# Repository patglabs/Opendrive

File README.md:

# Opendrive
This is currently the first prototype for a open source Field-Oriented Control Electronic Speed Controller.

I am currently designing it to be able to drive 300w motors at 12v (or 3s).

This doesnt mean these are limitation. With good cooling they should be able to handle quite a bit more.

It's designed to be used on a robotic arm I'm working on.

For Groundplane:
the template gives a 404

UPDATE:
yeah its gonna be too expensive nvm

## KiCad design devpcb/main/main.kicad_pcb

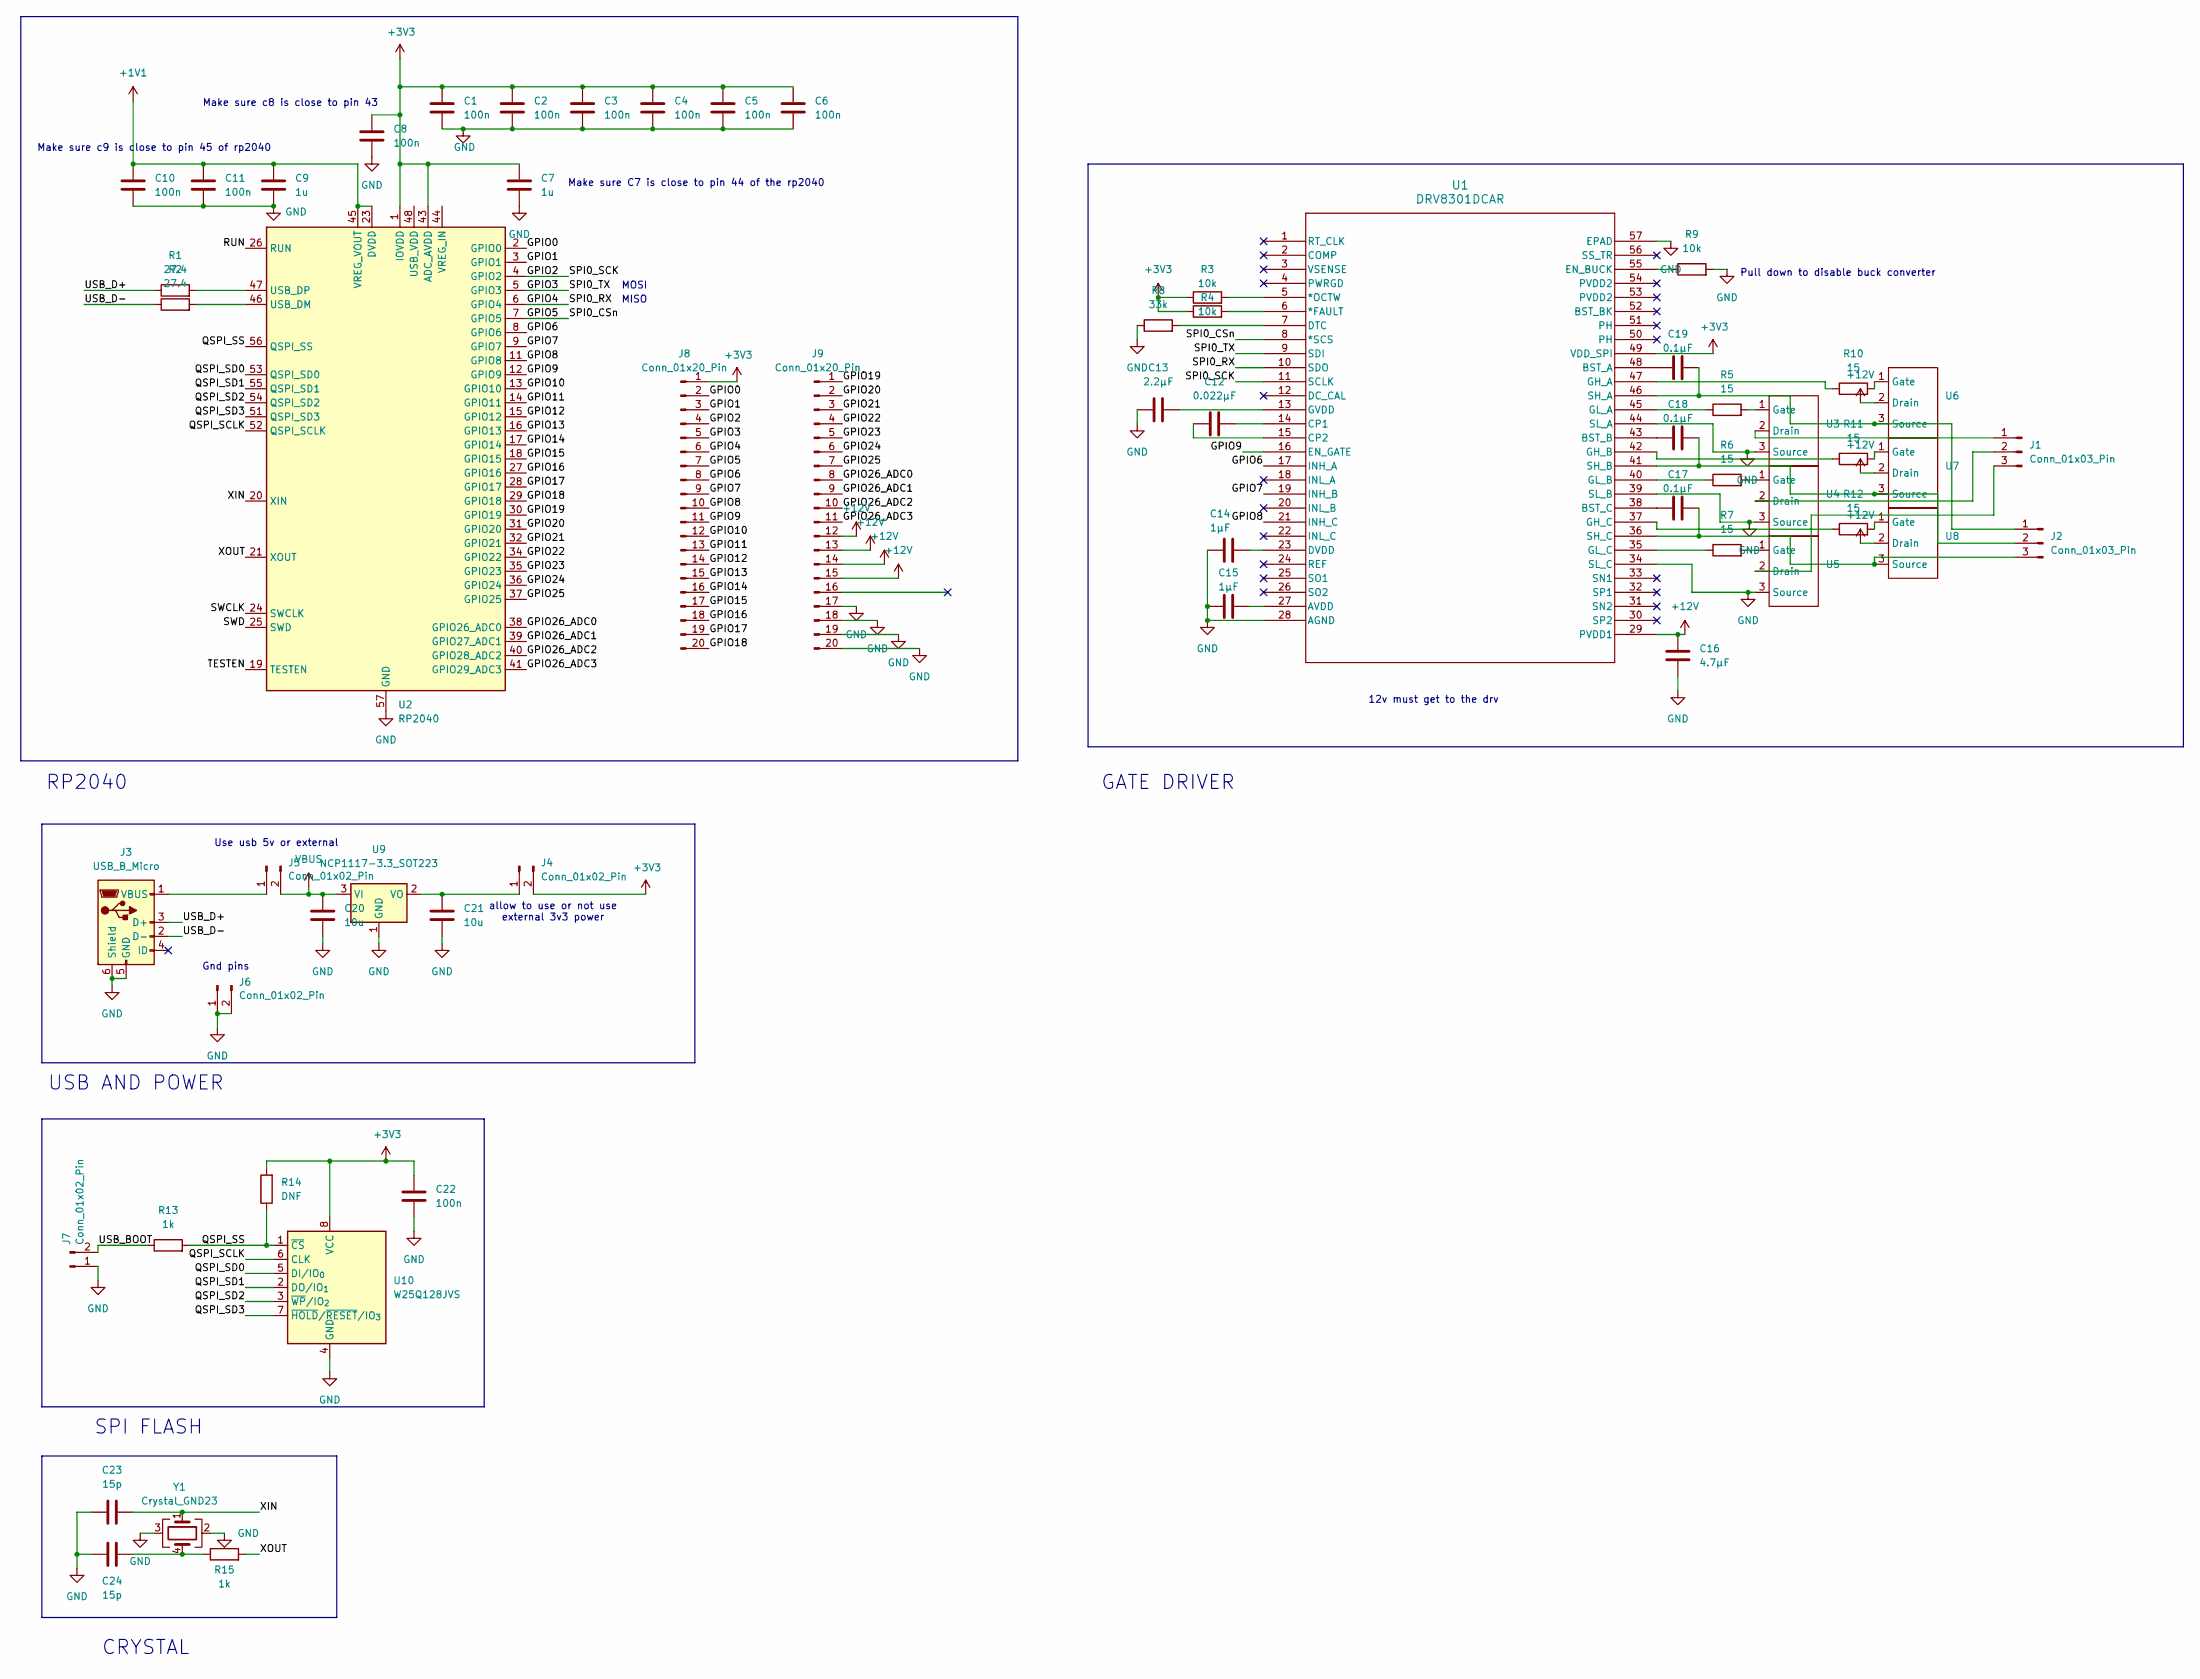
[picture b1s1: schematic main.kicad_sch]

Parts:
C1, C2, C3, C4, C5, C6, C8, C10, C11, C22: 100n; C_0402_1005Metric
C7, C9: 1u; C_0603_1608Metric
C12: 0.022µF; C_0402_1005Metric_Pad0.74x0.62mm_HandSolder
C13: 2.2µF; C_0805_2012Metric
C14, C15: 1µF; C_0603_1608Metric
C16: 4.7µF; C_0805_2012Metric
C17, C18, C19: 0.1µF; C_0603_1608Metric
C20, C21: 10u; C_0805_2012Metric
C23, C24: 15p; C_0402_1005Metric
J1, J2: Conn_01x03_Pin; PinHeader_1x03_P2.54mm_Vertical
J3: USB_B_Micro; USB_Micro-AB_Molex_47590-0001
J4, J5, J6, J7: Conn_01x02_Pin; PinHeader_1x02_P2.54mm_Vertical
J8, J9: Conn_01x20_Pin; PinHeader_1x20_P2.54mm_Vertical
R1, R2: 27.4; R_0402_1005Metric
R3, R4, R9: 10k; R_0402_1005Metric
R5, R6, R7, R10, R11, R12: 15; R_0402_1005Metric
R8: 33k; R_0402_1005Metric
R13, R15: 1k; R_0402_1005Metric
R14: DNF; R_0402_1005Metric
U1: DRV8301DCAR; DCA56_6P35X3P61
U2: RP2040; QFN-56-1EP_7x7mm_P0.4mm_EP3.2x3.2mm
U3, U4, U5, U6, U7, U8: TO-220-3_Vertical
U9: NCP1117-3.3_SOT223; SOT-223-3_TabPin2
U10: W25Q128JVS; SOIC-8_5.3x5.3mm_P1.27mm
Y1: Crystal_GND23; Crystal_SMD_3225-4Pin_3.2x2.5mm

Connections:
+1V1: C9.1, C10.1, C11.1, U2.23 (DVDD), U2.45 (VREG_VOUT), U2.50 (DVDD)
+3V3: C1.1, C2.1, C3.1, C4.1, C5.1, C6.1, C7.1, C8.1, C22.1, J4.2, J8.1, R3.1, R4.1, R14.2, U1.49 (VDD_SPI), U2.1 (IOVDD), U2.10 (IOVDD), U2.22 (IOVDD), U2.33 (IOVDD), U2.42 (IOVDD), U2.43 (ADC_AVDD), U2.49 (IOVDD), U10.8 (VCC)
+12V: C16.1, J9.12, J9.13, J9.14, J9.15, U1.29 (PVDD1), U6.2 (Drain), U7.2 (Drain), U8.2 (Drain)
/GPIO0: J8.2, U2.2 (GPIO0)
/GPIO1: J8.3, U2.3 (GPIO1)
/GPIO2: J8.4, U1.11 (SCLK), U2.4 (GPIO2)
/GPIO3: J8.5, U1.9 (SDI), U2.5 (GPIO3)
/GPIO4: J8.6, U1.10 (SDO), U2.6 (GPIO4)
/GPIO5: J8.7, U1.8 (*SCS), U2.7 (GPIO5)
/GPIO6: J8.8, U1.17 (INH_A), U2.8 (GPIO6)
/GPIO7: J8.9, U1.19 (INH_B), U2.9 (GPIO7)
/GPIO8: J8.10, U1.21 (INH_C), U2.11 (GPIO8)
/GPIO9: J8.11, U1.16 (EN_GATE), U2.12 (GPIO9)
/GPIO10: J8.12, U2.13 (GPIO10)
/GPIO11: J8.13, U2.14 (GPIO11)
/GPIO12: J8.14, U2.15 (GPIO12)
/GPIO13: J8.15, U2.16 (GPIO13)
/GPIO14: J8.16, U2.17 (GPIO14)
/GPIO15: J8.17, U2.18 (GPIO15)
/GPIO16: J8.18, U2.27 (GPIO16)
/GPIO17: J8.19, U2.28 (GPIO17)
/GPIO18: J8.20, U2.29 (GPIO18)
/GPIO19: J9.1, U2.30 (GPIO19)
/GPIO20: J9.2, U2.31 (GPIO20)
/GPIO21: J9.3, U2.32 (GPIO21)
/GPIO22: J9.4, U2.34 (GPIO22)
/GPIO23: J9.5, U2.35 (GPIO23)
/GPIO24: J9.6, U2.36 (GPIO24)
/GPIO25: J9.7, U2.37 (GPIO25)
/GPIO26_ADC0: J9.8, U2.38 (GPIO26_ADC0)
/GPIO26_ADC1: J9.9, U2.39 (GPIO27_ADC1)
/GPIO26_ADC2: J9.10, U2.40 (GPIO28_ADC2)
/GPIO26_ADC3: J9.11, U2.41 (GPIO29_ADC3)
/QSPI_SCLK: U2.52 (QSPI_SCLK), U10.6 (CLK)
/QSPI_SD0: U2.53 (QSPI_SD0), U10.5 (DI/IO_{0})
/QSPI_SD1: U2.55 (QSPI_SD1), U10.2 (DO/IO_{1})
/QSPI_SD2: U2.54 (QSPI_SD2), U10.3 (~WP/IO_{2})
/QSPI_SD3: U2.51 (QSPI_SD3), U10.7 (~HOLD/~RESET/IO_{3})
/QSPI_SS: R13.2, R14.1, U2.56 (QSPI_SS), U10.1 (~CS)
/RUN: U2.26 (RUN)
/SWCLK: U2.24 (SWCLK)
/SWD: U2.25 (SWD)
/TESTEN: U2.19 (TESTEN)
/USB_BOOT: J7.2, R13.1
/USB_D+: J3.3 (D+), R1.1
/USB_D-: J3.2 (D-), R2.1
/XIN: C23.2, U2.20 (XIN), Y1.1
/XOUT: R15.2, U2.21 (XOUT)
GND: C1.2, C2.2, C3.2, C4.2, C5.2, C6.2, C7.2, C8.2, C9.2, C10.2, C11.2, C13.1, C14.1, C15.1, C16.2, C20.2, C21.2, C22.2, C23.1, C24.1, J3.5 (GND), J3.6 (Shield), J6.1, J6.2, J7.1, J9.17, J9.18, J9.19, J9.20, R8.1, R9.2, U1.28 (AGND), U1.34 (SL_C), U1.39 (SL_B), U1.44 (SL_A), U1.57 (EPAD), U2.57 (GND), U3.3 (Source), U4.3 (Source), U5.3 (Source), U9.1 (GND), U10.4 (GND), Y1.2, Y1.3
unnamed: C24.2, R15.1, Y1.4
unnamed: J1.1, U3.2 (Drain)
unnamed: J1.2, U4.2 (Drain)
unnamed: J1.3, U5.2 (Drain)
unnamed: C19.2, J2.1, U1.46 (SH_A), U6.3 (Source)
unnamed: C18.2, J2.2, U1.41 (SH_B), U7.3 (Source)
unnamed: C17.2, J2.3, U1.36 (SH_C), U8.3 (Source)
unnamed: J3.1 (VBUS), J5.1
unnamed: C21.1, J4.1, U9.2 (VO)
unnamed: R4.2, U1.6 (*FAULT)
unnamed: R3.2, U1.5 (*OCTW)
unnamed: C15.2, U1.27 (AVDD)
unnamed: C19.1, U1.48 (BST_A)
unnamed: C18.1, U1.43 (BST_B)
unnamed: C17.1, U1.38 (BST_C)
unnamed: C12.2, U1.14 (CP1)
unnamed: C12.1, U1.15 (CP2)
unnamed: R8.2, U1.7 (DTC)
unnamed: C14.2, U1.23 (DVDD)
unnamed: R9.1, U1.55 (EN_BUCK)
unnamed: R10.1, U1.47 (GH_A)
unnamed: R11.1, U1.42 (GH_B)
unnamed: R12.1, U1.37 (GH_C)
unnamed: R5.1, U1.45 (GL_A)
unnamed: R6.1, U1.40 (GL_B)
unnamed: R7.1, U1.35 (GL_C)
unnamed: C13.2, U1.13 (GVDD)
unnamed: R2.2, U2.46 (USB_DM)
unnamed: R1.2, U2.47 (USB_DP)
unnamed: R5.2, U3.1 (Gate)
unnamed: R6.2, U4.1 (Gate)
unnamed: R7.2, U5.1 (Gate)
unnamed: R10.2, U6.1 (Gate)
unnamed: R11.2, U7.1 (Gate)
unnamed: R12.2, U8.1 (Gate)
VBUS: C20.1, J5.2, U9.3 (VI)

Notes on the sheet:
allow to use or not use external 3v3 power
Use usb 5v or external
MOSI
SPI FLASH
12v must get to the drv
GATE DRIVER
USB AND POWER
CRYSTAL
Gnd pins
Make sure c8 is close to pin 43
Pull down to disable buck converter
RP2040
MISO
Make sure c9 is close to pin 45 of rp2040
Make sure C7 is close to pin 44 of the rp2040

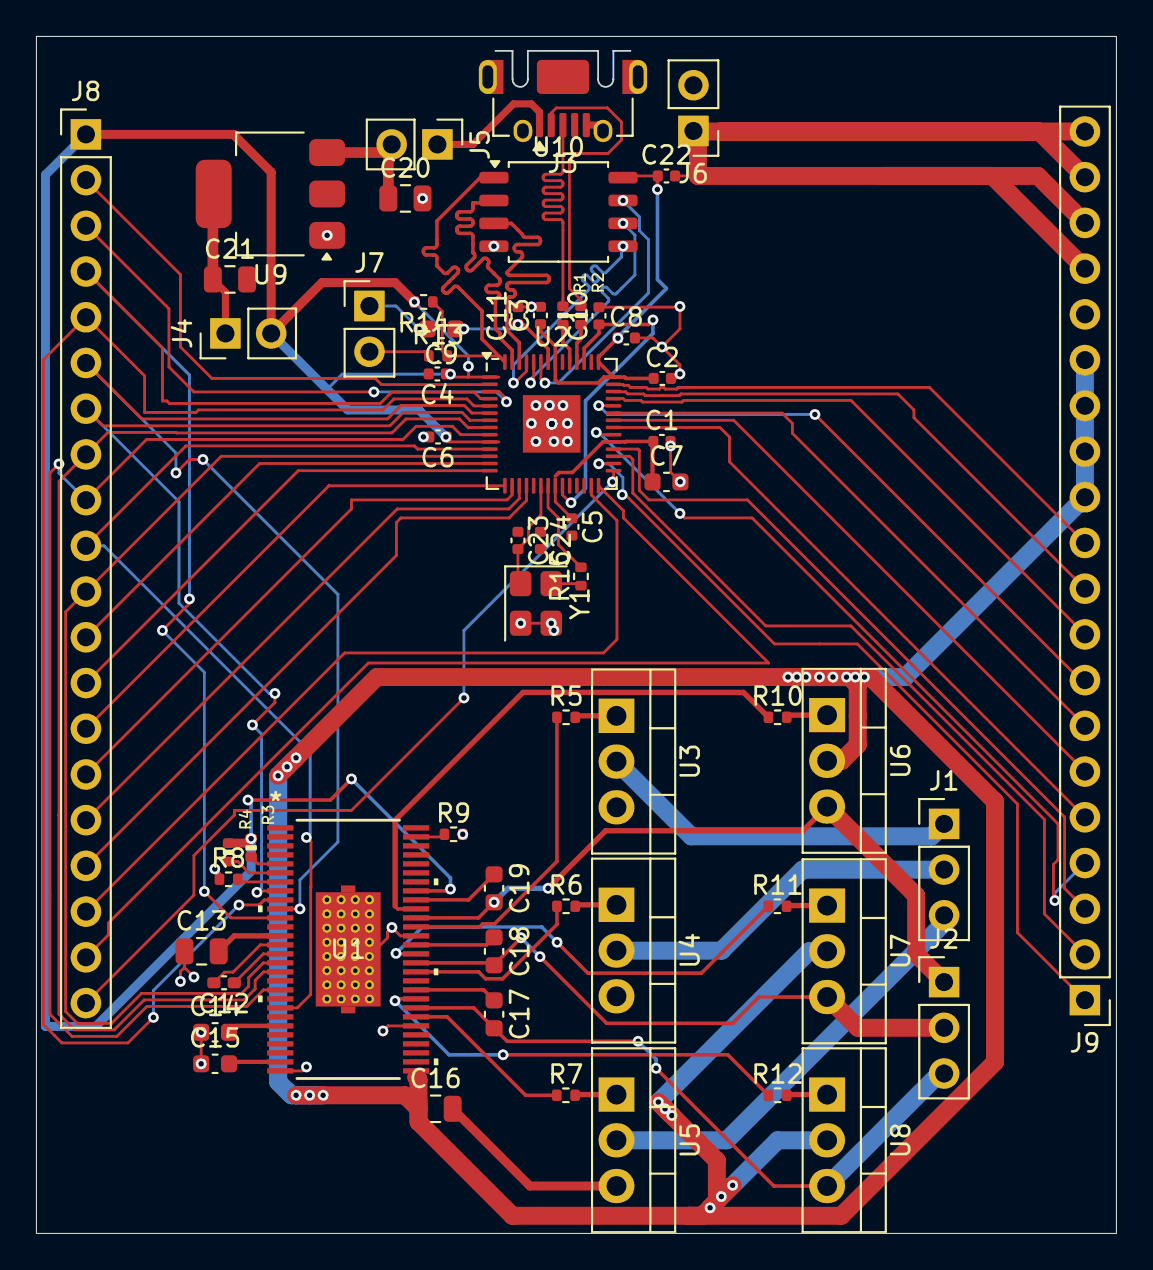
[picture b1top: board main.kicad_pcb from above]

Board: 2 copper layers, 59.9 x 66.5 mm, 59 parts (0 on the bottom side), 81 nets.

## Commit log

2026-04-24 Add update about project expense considerations
    Add update note regarding project cost concerns.
